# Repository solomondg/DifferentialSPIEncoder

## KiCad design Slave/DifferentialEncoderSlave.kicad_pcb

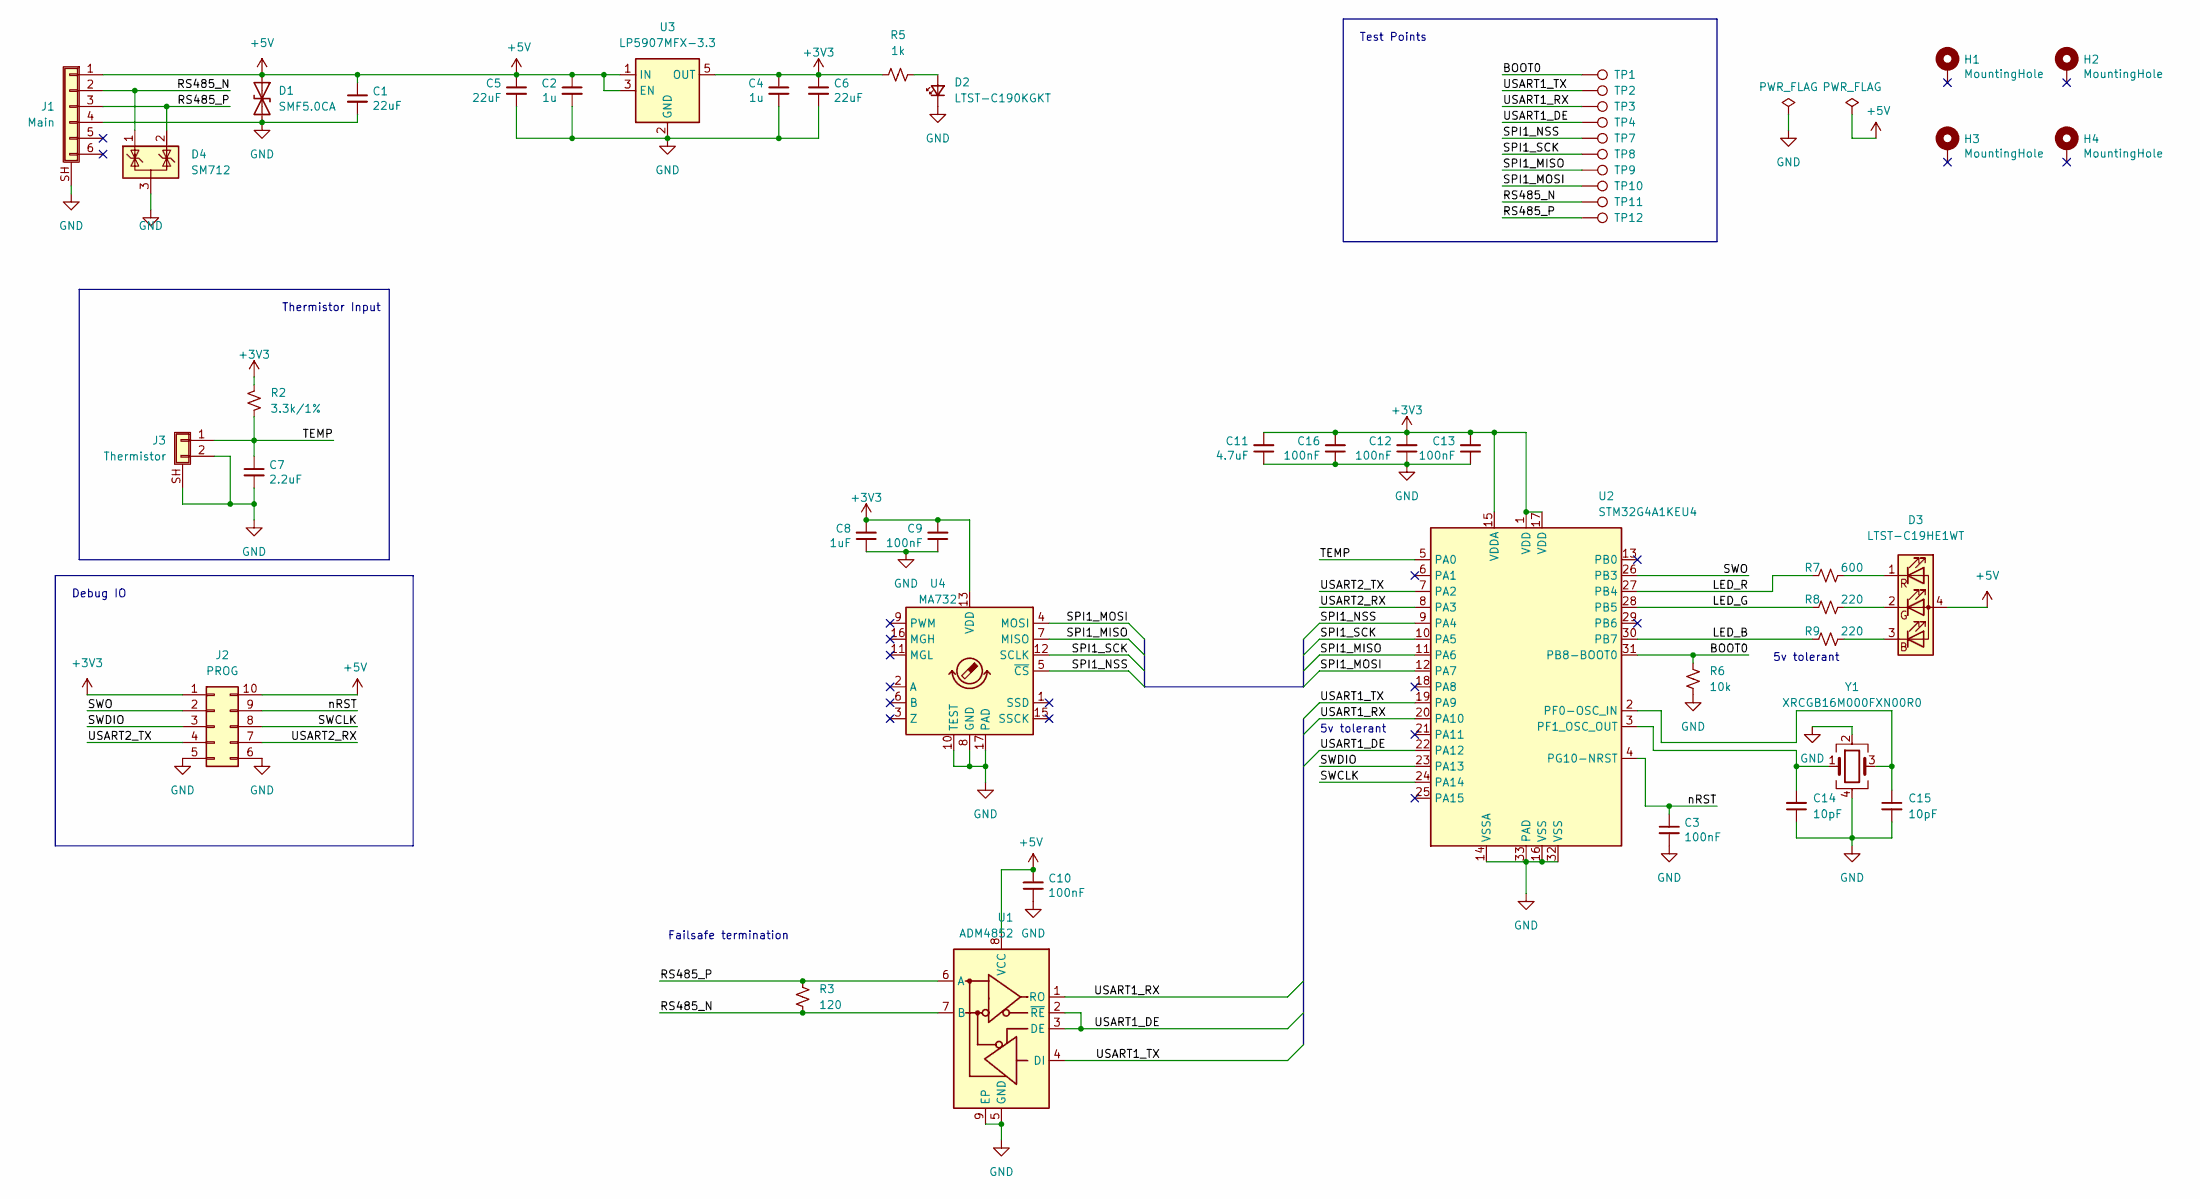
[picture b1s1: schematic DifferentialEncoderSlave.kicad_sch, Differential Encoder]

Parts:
C1, C5, C6: 22uF; C_0805_2012Metric
C2, C4: 1u; C_0402_1005Metric
C3, C9, C10, C12, C13, C16: 100nF; C_0402_1005Metric
C7: 2.2uF; C_0402_1005Metric
C8: 1uF; C_0402_1005Metric
C11: 4.7uF; C_0603_1608Metric
C14, C15: 10pF; C_0402_1005Metric
D1: SMF5.0CA; D_SOD-123F
D2: LTST-C190KGKT; LED_0603_1608Metric
D3: LTST-C19HE1WT; LED_LiteOn_LTST-C19HE1WT
D4: SM712; SOT-23
H1, H2, H3, H4: MountingHole; MountingHole_3.1mm_Pad_Via
J1: Main; Molex_CLIK-Mate_502585-0670_1x06-1MP_P1.50mm_Horizontal
J2: PROG; Tag-Connect_TC2050-IDC-NL_2x05_P1.27mm_Vertical_with_bottom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
J3: Thermistor; JST_GH_SM02B
R2: 3.3k/1%; R_0402_1005Metric
R3: 120; R_0805_2012Metric
R5: 1k; R_0402_1005Metric
R6: 10k; R_0402_1005Metric
R7: 600; R_0402_1005Metric
R8, R9: 220; R_0402_1005Metric
TP1, TP2, TP3, TP4, TP7, TP8, TP9, TP10, TP11, TP12: TestPoint; TestPoint_Pad_1.0x1.0mm
U1: ADM4852; LFCSP-8-1EP_3x3mm_P0.5mm_EP1.45x1.74mm
U2: STM32G4A1KEU4; UFQFPN-32-1EP_5x5mm_P0.5mm_EP3.5x3.5mm
U3: LP5907MFX-3.3; SOT-23-5
U4: MA732; QFN-16-1EP_3x3mm_P0.5mm_EP1.7x1.7mm
Y1: XRCGB16M000FXN00R0; Crystal_SMD_2016-4Pin_2.0x1.6mm

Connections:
+3V3: C4.1, C6.1, C8.2, C9.2, C11.2, C12.2, C13.2, C16.2, J2.1, R2.1, R5.1, U2.1 (VDD), U2.15 (VDDA), U2.17 (VDD), U3.5 (OUT), U4.13 (VDD)
+5V: C1.1, C2.1, C5.1, C10.2, D1.1 (A1), D3.4 (A), J1.1, J2.10, U1.8 (VCC), U3.1 (IN), U3.3 (EN)
/BOOT0: R6.1, TP1.1, U2.31 (PB8-BOOT0)
/LED_B: R9.1, U2.30 (PB7)
/LED_G: R8.1, U2.28 (PB5)
/LED_R: R7.1, U2.27 (PB4)
/RS485_N: D4.1 (K), J1.2, R3.2, TP11.1, U1.7 (B)
/RS485_P: D4.2 (K), J1.3, R3.1, TP12.1, U1.6 (A)
/SPI1_MISO: TP9.1, U2.11 (PA6), U4.7 (MISO)
/SPI1_MOSI: TP10.1, U2.12 (PA7), U4.4 (MOSI)
/SPI1_NSS: TP7.1, U2.9 (PA4), U4.5 (~CS)
/SPI1_SCK: TP8.1, U2.10 (PA5), U4.12 (SCLK)
/SWCLK: J2.8, U2.24 (PA14)
/SWDIO: J2.3, U2.23 (PA13)
/SWO: J2.2, U2.26 (PB3)
/TEMP: C7.1, J3.1, R2.2, U2.5 (PA0)
/USART1_DE: TP4.1, U1.2 (~RE), U1.3 (DE), U2.22 (PA12)
/USART1_RX: TP3.1, U1.1 (RO), U2.20 (PA10)
/USART1_TX: TP2.1, U1.4 (DI), U2.19 (PA9)
/USART2_RX: J2.7, U2.8 (PA3)
/USART2_TX: J2.4, U2.7 (PA2)
/nRST: C3.1, J2.9, U2.4 (PG10-NRST)
GND: C1.2, C2.2, C3.2, C4.2, C5.2, C6.2, C7.2, C8.1, C9.1, C10.1, C11.1, C12.1, C13.1, C14.1, C15.2, C16.1, D1.2 (A2), D2.1 (K), D4.3 (A), J1.4, J1.SH (Shield), J2.5, J2.6, J3.2, J3.SH (Shield), R6.2, U1.5 (GND), U1.9 (EP), U2.14 (VSSA), U2.16 (VSS), U2.32 (VSS), U2.33 (PAD), U3.2 (GND), U4.8 (GND), U4.10 (TEST), U4.17 (PAD), Y1.2, Y1.4
unnamed: C14.2, U2.3 (PF1_OSC_OUT), Y1.1
unnamed: C15.1, U2.2 (PF0-OSC_IN), Y1.3
unnamed: D2.2 (A), R5.2
unnamed: D3.1 (RK), R7.2
unnamed: D3.2 (GK), R8.2
unnamed: D3.3 (BK), R9.2

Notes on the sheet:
Test Points
Thermistor Input
5v tolerant
Failsafe termination
Debug IO

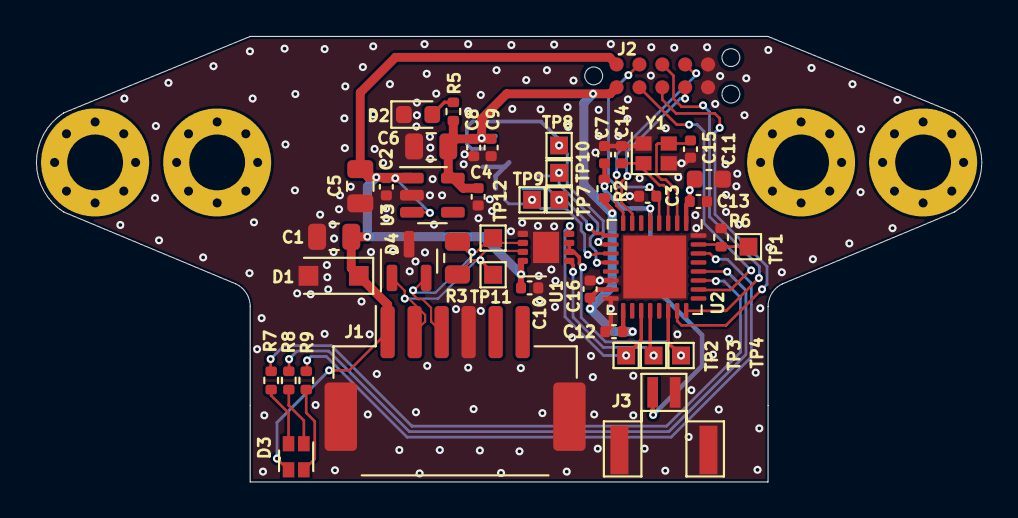
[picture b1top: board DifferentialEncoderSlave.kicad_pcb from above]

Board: 4 copper layers, 52.5 x 24.8 mm, 49 parts (1 on the bottom side), 29 nets.

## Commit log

2022-09-13 Solomon redux
